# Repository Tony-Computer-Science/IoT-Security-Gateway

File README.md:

# IoT Security Gateway

**CyberGuards, CSE 484.** Two ESP32 gateway boards connect devices on a
private WPA2 access point to an existing Wi-Fi network through a wired link
(SPI by default, with an optional two-wire UART test mode).

```text
Devices -> Board A: WPA2 AP -> SPI/UART -> Board B: Wi-Fi station -> Router -> Internet
```

The board names remain **station-board (A)** and **bridge-board (B)** for
repository compatibility. These names do not describe their new Wi-Fi modes:
A is the access point; B is the upstream station. A third ESP32-C6 or ESP32-S3 (Board C)
joins A's AP and controls an RGB LED through a separate PC web service.

## Repository guide

| Path | Contents |
|---|---|
| [firmware/](firmware/README.md) | Gateway A/B images, Board C LED target, S3 SPI test host and shared components |
| [web/](web/README.md) | Browser interface, real-device PC service and standalone development mock |
| [hardware/](hardware/README.md) | S3 Rev A PCB and separate C6 SPI/UART wiring |
| [docs/](docs/README.md) | Architecture, API/link contracts, client setup, maintenance and testing |
| [tools/test/](tools/test/README.md) | Host protocol tests, HTTP tests, optional Postman checks and echo server |

For local UI work without boards, run `python3 web/mock/server.py` and open
the printed URL. The mock simulates the target; use the real-device service
in the setup below for physical LED control.

## Setting Up

The website and its API are a **separate service running outside the ESP32
boards**. For simplicity, this demo runs that service on a local computer
instead of a dedicated server: **the computer acts as the server**. It joins
**IoT-Gateway** and serves the UI/API at **http://192.168.78.10:8000/**.
Board C has that server IPv4 address and device TLS port **8443**
**compiled into its firmware**
from menuconfig (`TARGET_UI_HOST` / `TARGET_UI_PORT`); it does not discover
the server automatically. Board C contacts it over Wi-Fi; station and bridge
provide networking. No ESP32 hosts the website or browser API.

Before the first run, build/configure and flash each board using the
[station](firmware/station-board/README.md),
[bridge](firmware/bridge-board/README.md) and
[IoT device](firmware/target-device/README.md) instructions. Bridge needs the
upstream Wi-Fi credentials; Board C needs the separate station AP password.
Provision private device identities before the target build using
[PC-only isolation](docs/device-isolation.md). Keep passwords and identities
in private configuration, not this README.

1. **Power on station and bridge.** Keep their configured wired link connected.
   For SPI, match each configured signal at both ends, including handshake and
   common ground; see [C6 wiring](hardware/docs/README.md#esp32-c6-development-board-wiring).
   The current bench uses a private pin-map variant recorded in
   [testing](docs/testing.md). UART is an optional alternative and requires
   matching mode/baud and crossed TX/RX; see [UART wiring](docs/uart-link.md).
   Each board also needs USB power. Check the controllable RGB LEDs against
   the table below. Their identity colors do not prove Wi-Fi or internet access.
2. **Join the station network from a phone and check internet access.** In
   the phone's Wi-Fi settings, join **IoT-Gateway** using the station AP
   password. Temporarily turn off mobile data so the test uses the gateway.
   Open `http://example.com` and confirm the page loads; do not rely only on
   the phone's connection label. If it fails, check that the phone joined
   **IoT-Gateway** and that bridge joined the intended upstream network
   (the configured school network, using passwordless OWE) with
   a valid IP address. Use the troubleshooting
   table below before proceeding with the internet test.
3. **Connect the computer that will host the web service.** Join that computer
   to **IoT-Gateway** too. On the Windows demo PC, set Wi-Fi IPv4 to
   **192.168.78.10**, subnet mask **255.255.255.0**, gateway **192.168.78.1**,
   and the upstream DNS supplied by bridge. Follow the
   [Windows fixed-IP and firewall steps](docs/client-network.md#windows-ui-computer).
   Check `ipconfig` shows .10 on the Wi-Fi adapter. Only this computer should
   use .10; the phone and IoT device obtain addresses automatically.
4. **Start the web service on that computer.** With Python 3.9 or later,
   open a terminal in this repository's root and run:

   ```powershell
   python web/device_server.py --host 192.168.78.10 --port 8000
   ```

   Leave the terminal open. Allow the device TLS listener on TCP 8443 using the
   scoped firewall rule in the Windows guide. On the PC, open
   `http://192.168.78.10:8000/`. Sign in as **operator** with the password
   printed by the service. This login password is separate from the Wi-Fi
   password. Use `device_server.py` for hardware control; the mock server
   only simulates a device. Until Board C connects, unavailable device status
   and disabled command buttons are expected.

   The service also monitors the gateway live: it pings Board A
   (`192.168.78.1`) every 2 s and opens a connection to `1.1.1.1:443` through
   A, the UART link and Board B every 5 s. The control page shows each result
   with a five-minute up/down timeline, and changes appear in the event log.
   The path check is only meaningful while this computer routes through
   Board A, so keep it off other networks (Ethernet, a second Wi-Fi) during
   the demo. Use `--outside IPv4:port` if the upstream network blocks that
   address.
5. **Power on the third C6, the IoT device.** Its firmware must have the
   **IoT-Gateway** SSID/passphrase, service address **192.168.78.10**, port
   **8443** for the authenticated device channel, and device ID **iot-c6**.
   Provision identities before building as described in
   [PC-only isolation](docs/device-isolation.md). It joins Wi-Fi automatically and polls
   the service; it needs no signal jumpers to the other boards. Wait for
   reachable status in the website, then click **Turn on**: its controllable
   RGB LED should become **green** after device confirmation. Click **Turn
   off** and verify it goes dark. Off at startup is expected, not a connection
   failure. Station remains blue and bridge remains red.

| Board | Expected controllable RGB LED |
|---|---|
| Station / A | **Blue**, identifying the station firmware |
| Bridge / B | **Red**, identifying the bridge firmware |
| IoT device / C | **Off at startup**, **green after Turn on**, off after Turn off |

Look at the controllable RGB LED, not the separate power light, which may
stay green. These defaults apply to the matching C6 development boards with
the RGB LED on GPIO8. The phone, service PC and IoT device use three of the
station AP's four default client slots.

If a check fails:

| Symptom | What to check |
|---|---|
| Wrong board color or IoT-Gateway is missing | Confirm power, board labels and the correct firmware image. Check AP configuration and startup logs; a power light alone does not identify the firmware. |
| Phone joins but a webpage cannot load | Confirm mobile data is off, the phone joined IoT-Gateway and DHCP gave it 192.168.78.100–199 with gateway .1. Check bridge's upstream SSID/password and IP, and test that upstream network's internet separately. Check the selected SPI signal mapping/handshake and common ground, or crossed UART wires and matching mode/baud if UART is selected. After bridge is online, reconnect the phone to refresh DHCP/DNS. |
| Service fails to bind to 192.168.78.10 | Confirm the service PC joined IoT-Gateway and .10 is assigned to its Wi-Fi adapter before launch. Check another program is not already using port 8000. |
| Website opens on the PC but not on the phone | Expected: the UI/API admits only the PC itself. Other clients receive 403 if they can reach the listener. |
| Website opens but the device stays unavailable | Confirm Board C is flashed/configured for IoT-Gateway with the AP password, .10:8443, provisioned TLS identities and matching device ID. Keep the real device service running. Inspect Board C's Wi-Fi/poll logs and the PC firewall. The LED can correctly be off while connected. |
| A command has an unknown result | Wait for a fresh device status report before retrying, then compare the reported state with the physical LED. Check service/device logs if confirmation continues to fail. |

Local website and LED control use the station AP and can work without
upstream internet; the phone's internet test checks a separate routing path.
No port forwarding or public exposure is needed for this local demo. A
dedicated server can host the separate service later, but Board C's configured
service IPv4 address/port and outbound network reachability must match that
deployment. The device channel requires mutual TLS; the UI/API is PC-only. See
the [isolation setup and limits](docs/device-isolation.md) and the
[device API and its limitations](docs/device-api.md).

## Current status

- Board B implements personal WPA2/WPA3 or passwordless OWE uplink,
  DHCP/reconnection, a bounded Ethernet-over-SPI/UART transport, IPv4
  routing/NAPT, and restart isolation.
- `firmware/spi-test-host` is a separate Board A test image. Its radio stays
  off; DNS/HTTPS and configurable TCP/UDP echo tests use SPI only.
- Board A implements an AP-only WPA2/AES network, DHCP, DNS propagation and
  client NAT onto SPI. Per-device network policy remains future work; the
  website/API runs as the separate service described above.
- Board C is an ESP32-C6 Wi-Fi LED device that contacts a PC at
  **192.168.78.10:8443** with mutual TLS. The PC serves the website on port 8000 and confirms LED
  commands against device acknowledgements. See [third-board setup](firmware/target-device/README.md).
  S3 physical LED/heartbeat/restart results are recorded in
  [bench evidence](docs/s3-test-evidence.md); the C6/Linux fixed-IP bench passed control; Windows acceptance is pending.
- ESP32-C6 UART hardware checks verified AP/DHCP, phone internet access and
  peer-restart recovery; see [UART results](docs/uart-link.md). The 4 MHz SPI
  bench passed DNS/HTTP with zero malformed frames. Simultaneous clients,
  restart recovery on SPI and extended soak checks remain on the
  [acceptance checklist](docs/testing.md).
- Four Wi-Fi clients are supported by default, with .10 excluded from DHCP
  for a fixed UI PC. See [Windows setup and outbound-only routing](docs/client-network.md).

## Build and use

Use **ESP-IDF 6.1**, ESP32-S3 or ESP32-C6, at least 4 MB flash; PSRAM is not
required. The Rev A PCB and default target remain S3. C6 development boards
use the separate [C6 wiring](hardware/docs/README.md#esp32-c6-development-board-wiring)
and `idf.py set-target esp32c6` in each station/bridge project.
See [Board A instructions](firmware/station-board/README.md),
[Board B instructions](firmware/bridge-board/README.md) and
[test-host instructions](firmware/spi-test-host/README.md) for configuration,
flashing, wiring, and tests. Do not commit generated `sdkconfig` or binaries:
all Wi-Fi firmware binaries contain their configured credentials.

For the third C6, use [Board C instructions](firmware/target-device/README.md).
On the Windows UI PC, run `python web/device_server.py --host 192.168.78.10 --port 8000`
from this repository, then open `http://192.168.78.10:8000/` and use the
operator login printed by the service.

```sh
python3 tools/test/run_host_tests.py
python3 tools/test/test_device_server.py
python3 web/scripts/build.py
```

These local checks need Python 3.9+; protocol tests also need a C compiler
with AddressSanitizer/UndefinedBehaviorSanitizer. Board C parser tests require
its managed cJSON dependency, and the optional collection check requires the
Postman CLI. See [all test commands and prerequisites](docs/testing.md#local-software-checks).

## Design and requirements

This is an intentional change from the original fixed-target command gateway.
Normal internet routing conflicts with the original prohibition on packet
forwarding and with the original command allow-list. The original graded
[R1–R7 text](docs/requirements.md) is preserved verbatim; this milestone does
**not** claim compliance with that design. The differences and remaining
security work are explained in [architecture](docs/architecture.md).

Key references: [SPI contract 0.2.0](docs/spi-protocol.md),
[firmware maintenance](docs/firmware-maintenance.md),
[hardware pinout](hardware/docs/README.md), [contribution rules](CONTRIBUTING.md).
The existing KiCad layout is not fabricated; some silkscreen labels describe
the previous Wi-Fi roles. Rev A PCB wiring is unchanged; C6 boards use their
separate documented pinout.

For a demo with two signal jumpers plus common ground, station and bridge can
use the optional [UART test link](docs/uart-link.md). SPI remains the default.

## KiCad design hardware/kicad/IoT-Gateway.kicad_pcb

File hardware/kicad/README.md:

# hardware/kicad

KiCad 10 project for the gateway PCB: Board A and Board B (two ESP32-S3-WROOM-1
modules) on one 4-layer board, linked only by SPI (SCLK, MOSI, MISO, CS) and
the HS handshake line. Rev A is designed through ERC/DRC-clean outputs but not
fabricated.

## Current owner (provisional)

Carter Cattadoris. Any member may work here; the current owner reviews.

## Contents

| Path | Purpose |
|---|---|
| `IoT-Gateway.kicad_pro` | Project. Open this in KiCad 10 (files can't be opened by KiCad 9 or older) |
| `IoT-Gateway.kicad_sch` | Top sheet; sub-sheets `power.kicad_sch`, `module_a.kicad_sch`, `module_b.kicad_sch` |
| `IoT-Gateway.kicad_pcb` | 100 x 50 mm, 4 layers, JLCPCB JLC04161H-7628 stackup |
| `DESIGN_NOTES.md` | Requirements status, decisions and deviations log, power budget, stackup and routing notes |

Generated outputs (`outputs/`: schematic PDF, BOM, 3D renders, ERC/DRC
reports; `fab/`: Gerbers and drill files) and the Rev A generation scripts
(`scripts/`) are kept locally and git-ignored (see `.gitignore`). Regenerate
outputs from the KiCad files (File → Plot / Fabrication Outputs, or `kicad-cli`).

## Conventions

- Commit `.kicad_pro`, `.kicad_sch`, `.kicad_pcb`, and any project-local
  symbol and footprint libraries.
- Don't commit `*.kicad_prl`, `*-backups/`, or `fp-info-cache` (git-ignored).
- Put fabrication outputs (Gerbers, drill files) in `kicad/fab/` only when
  ordering a board, and tag the commit. `fab/` is git-ignored, so add them
  with `git add -f`.
- KiCad version: this project uses KiCad 10 (team version still to be agreed).

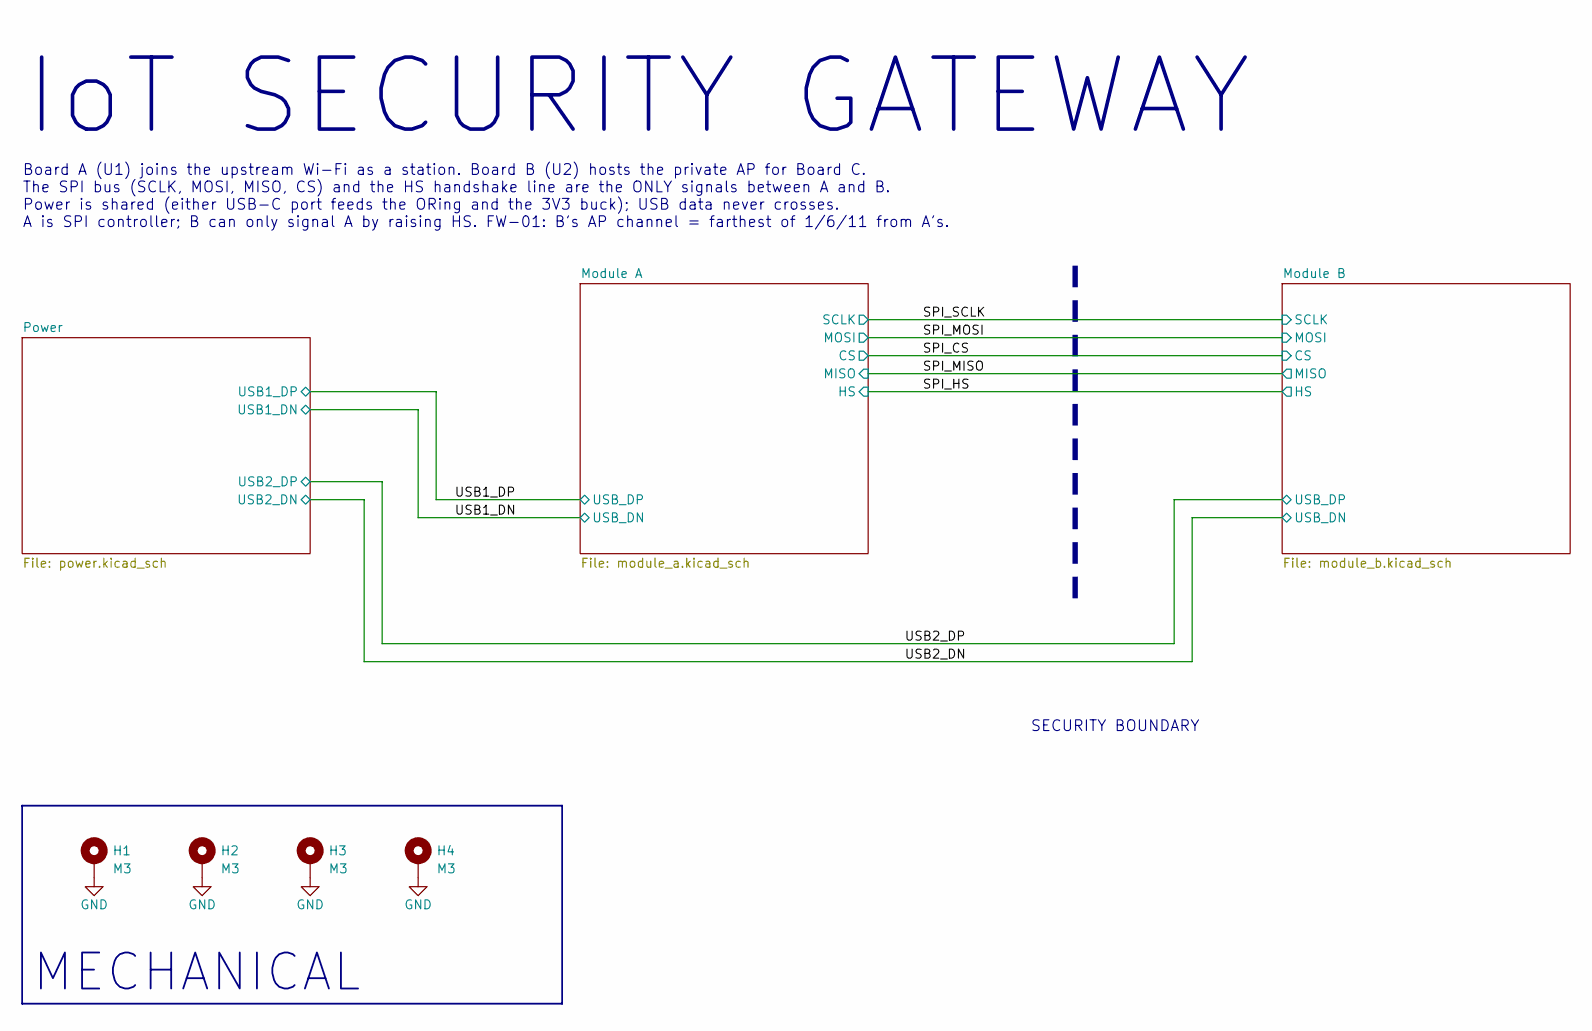
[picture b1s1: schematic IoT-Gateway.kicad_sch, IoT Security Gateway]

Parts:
H1, H2, H3, H4: M3; MountingHole_3.2mm_M3_Pad_Via

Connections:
GND: H1.1, H2.1, H3.1, H4.1; also elsewhere on the board

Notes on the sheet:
MECHANICAL
IoT SECURITY GATEWAY
Board A (U1) joins the upstream Wi-Fi as a station. Board B (U2) hosts the private AP for Board C. The SPI bus (SCLK, MOSI, MISO, CS) and the HS handshake line are the ONLY signals between A and B. Power is shared (either USB-C port feeds the ORing and the 3V3 buck); USB data never crosses. A is SP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
SECURITY BOUNDARY

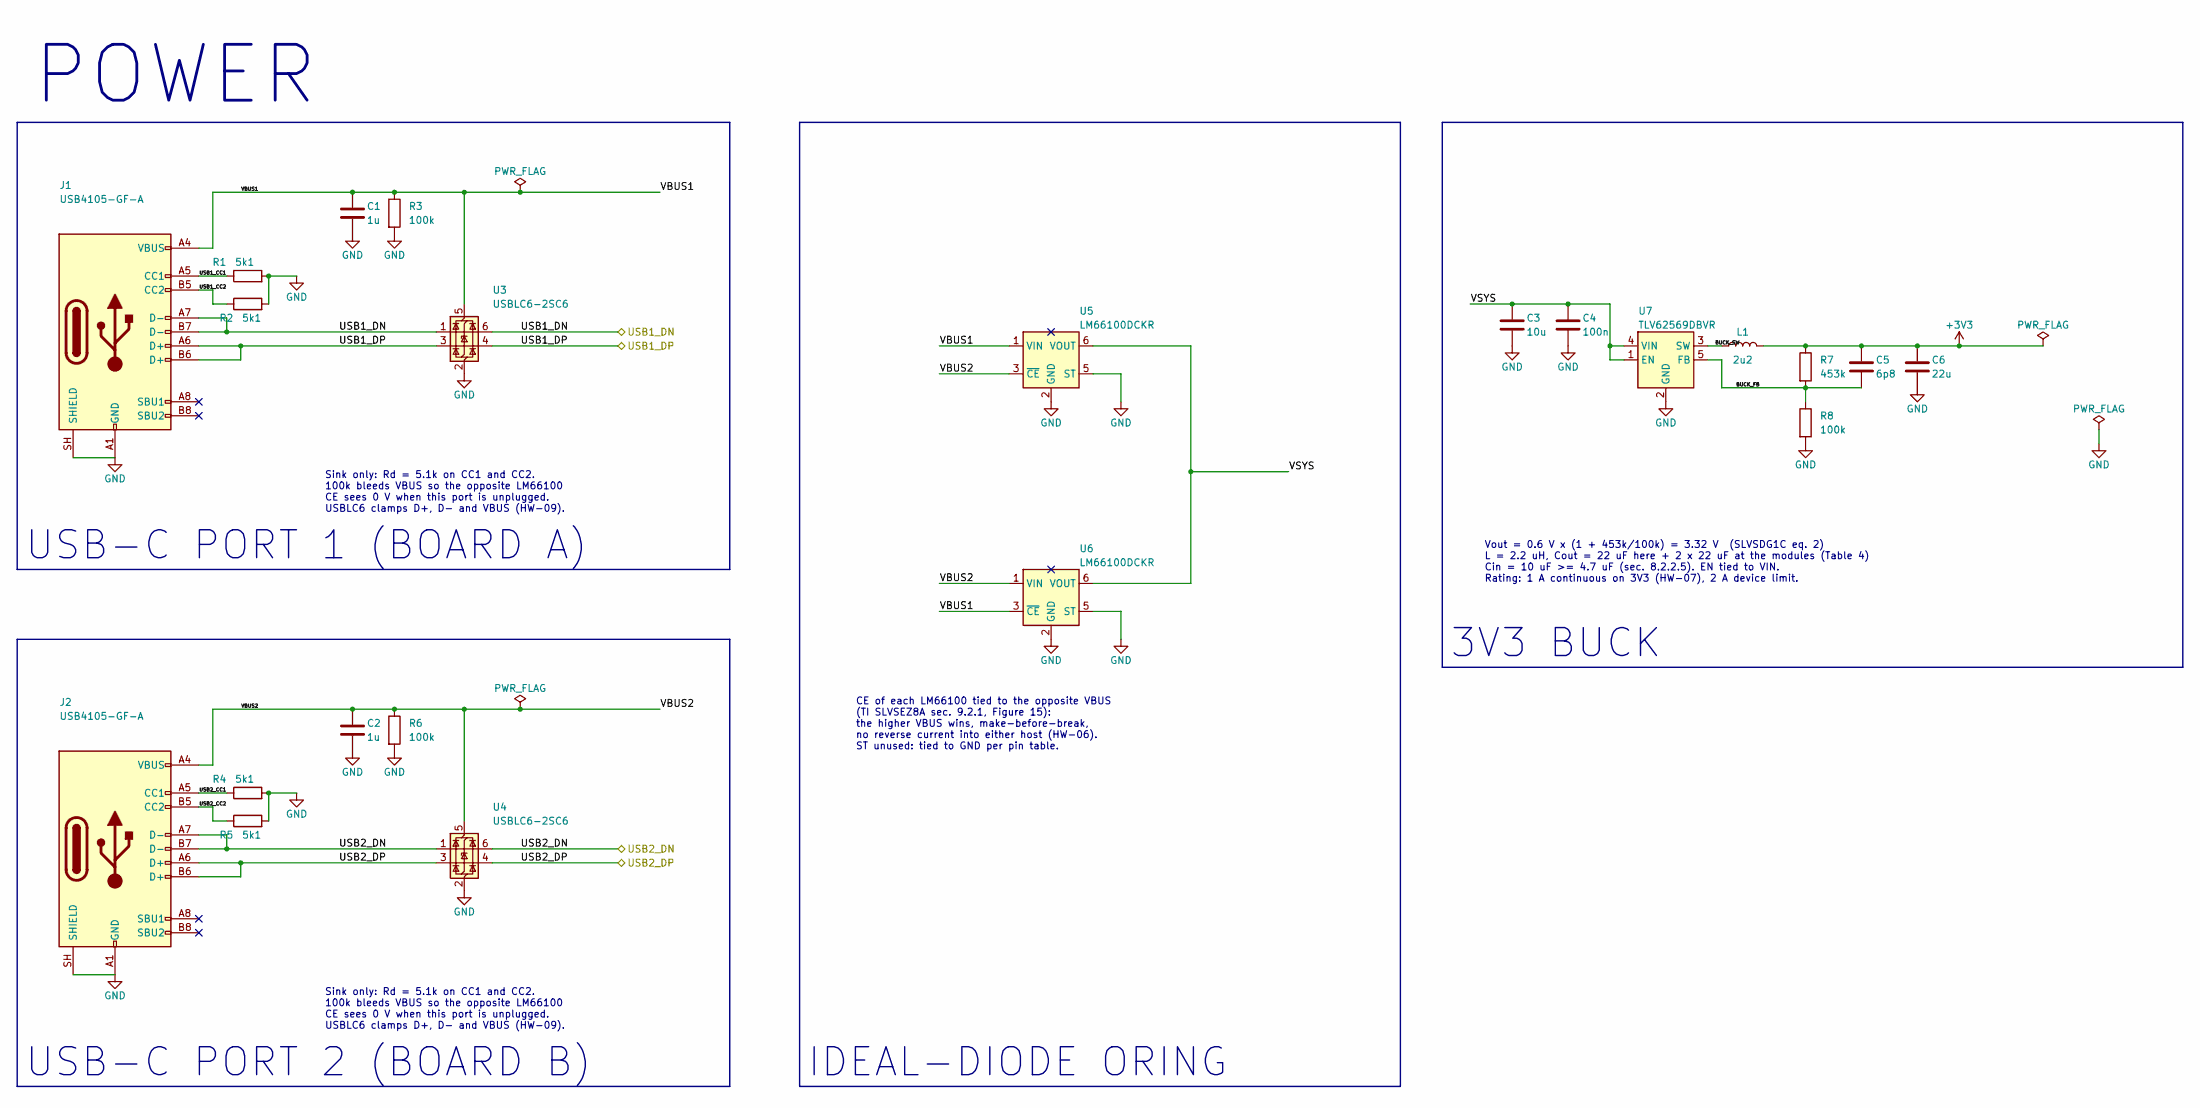
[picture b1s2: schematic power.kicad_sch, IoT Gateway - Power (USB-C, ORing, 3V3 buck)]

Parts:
C1, C2: 1u; C_0603_1608Metric
C3: 10u; C_0805_2012Metric
C4: 100n; C_0603_1608Metric
C5: 6p8; C_0603_1608Metric
C6: 22u; C_0805_2012Metric
J1, J2: USB4105-GF-A; USB_C_Receptacle_GCT_USB4105-xx-A_16P_TopMnt_Horizontal; Mfg Part # USB4105-GF-A
L1: 2u2; L_Coilcraft_XAL4020-XXX; Mfg Part # XAL4020-222ME
R1, R2, R4, R5: 5k1; R_0603_1608Metric
R3, R6, R8: 100k; R_0603_1608Metric
R7: 453k; R_0603_1608Metric
U3, U4: USBLC6-2SC6; SOT-23-6; Mfg Part # USBLC6-2SC6
U5, U6: LM66100DCKR; SOT-363_SC-70-6; Mfg Part # LM66100DCKR
U7: TLV62569DBVR; SOT-23-5; Mfg Part # TLV62569DBVR

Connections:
+3V3: C5.1, C6.1, L1.2, R7.1; also elsewhere on the board
/Power/BUCK_FB: C5.2, R7.2, R8.1, U7.5 (FB)
/Power/BUCK_SW: L1.1, U7.3 (SW)
/Power/USB1_CC1: J1.A5 (CC1), R1.1
/Power/USB1_CC2: J1.B5 (CC2), R2.1
/Power/USB2_CC1: J2.A5 (CC1), R4.1
/Power/USB2_CC2: J2.B5 (CC2), R5.1
/Power/VBUS1: C1.1, J1.A4 (VBUS), J1.A9 (VBUS), J1.B4 (VBUS), J1.B9 (VBUS), R3.1, U3.5 (VBUS), U5.1 (VIN), U6.3 (~CE)
/Power/VBUS2: C2.1, J2.A4 (VBUS), J2.A9 (VBUS), J2.B4 (VBUS), J2.B9 (VBUS), R6.1, U4.5 (VBUS), U5.3 (~CE), U6.1 (VIN)
/Power/VSYS: C3.1, C4.1, U5.6 (VOUT), U6.6 (VOUT), U7.1 (EN), U7.4 (VIN)
/USB1_DN: J1.A7 (D-), J1.B7 (D-), U3.1 (I/O1), U3.6 (I/O1); also elsewhere on the board
/USB1_DP: J1.A6 (D+), J1.B6 (D+), U3.3 (I/O2), U3.4 (I/O2); also elsewhere on the board
/USB2_DN: J2.A7 (D-), J2.B7 (D-), U4.1 (I/O1), U4.6 (I/O1); also elsewhere on the board
/USB2_DP: J2.A6 (D+), J2.B6 (D+), U4.3 (I/O2), U4.4 (I/O2); also elsewhere on the board
GND: C1.2, C2.2, C3.2, C4.2, C6.2, J1.A1 (GND), J1.A12 (GND), J1.B1 (GND), J1.B12 (GND), J1.SH (SHIELD), J2.A1 (GND), J2.A12 (GND), J2.B1 (GND), J2.B12 (GND), J2.SH (SHIELD), R1.2, R2.2, R3.2, R4.2, R5.2, R6.2, R8.2, U3.2 (GND), U4.2 (GND), U5.2 (GND), U5.5 (ST), U6.2 (GND), U6.5 (ST), U7.2 (GND); also elsewhere on the board

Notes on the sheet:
USB-C PORT 1 (BOARD A)
Sink only: Rd = 5.1k on CC1 and CC2. 100k bleeds VBUS so the opposite LM66100 CE sees 0 V when this port is unplugged. USBLC6 clamps D+, D- and VBUS (HW-09).
USB-C PORT 2 (BOARD B)
IDEAL-DIODE ORING
CE of each LM66100 tied to the opposite VBUS (TI SLVSEZ8A sec. 9.2.1, Figure 15): the higher VBUS wins, make-before-break, no reverse current into either host (HW-06). ST unused: tied to GND per pin table.
3V3 BUCK
Vout = 0.6 V x (1 + 453k/100k) = 3.32 V (SLVSDG1C eq. 2) L = 2.2 uH, Cout = 22 uF here + 2 x 22 uF at the modules (Table 4) Cin = 10 uF >= 4.7 uF (sec. 8.2.2.5). EN tied to VIN. Rating: 1 A continuous on 3V3 (HW-07), 2 A device limit.
POWER

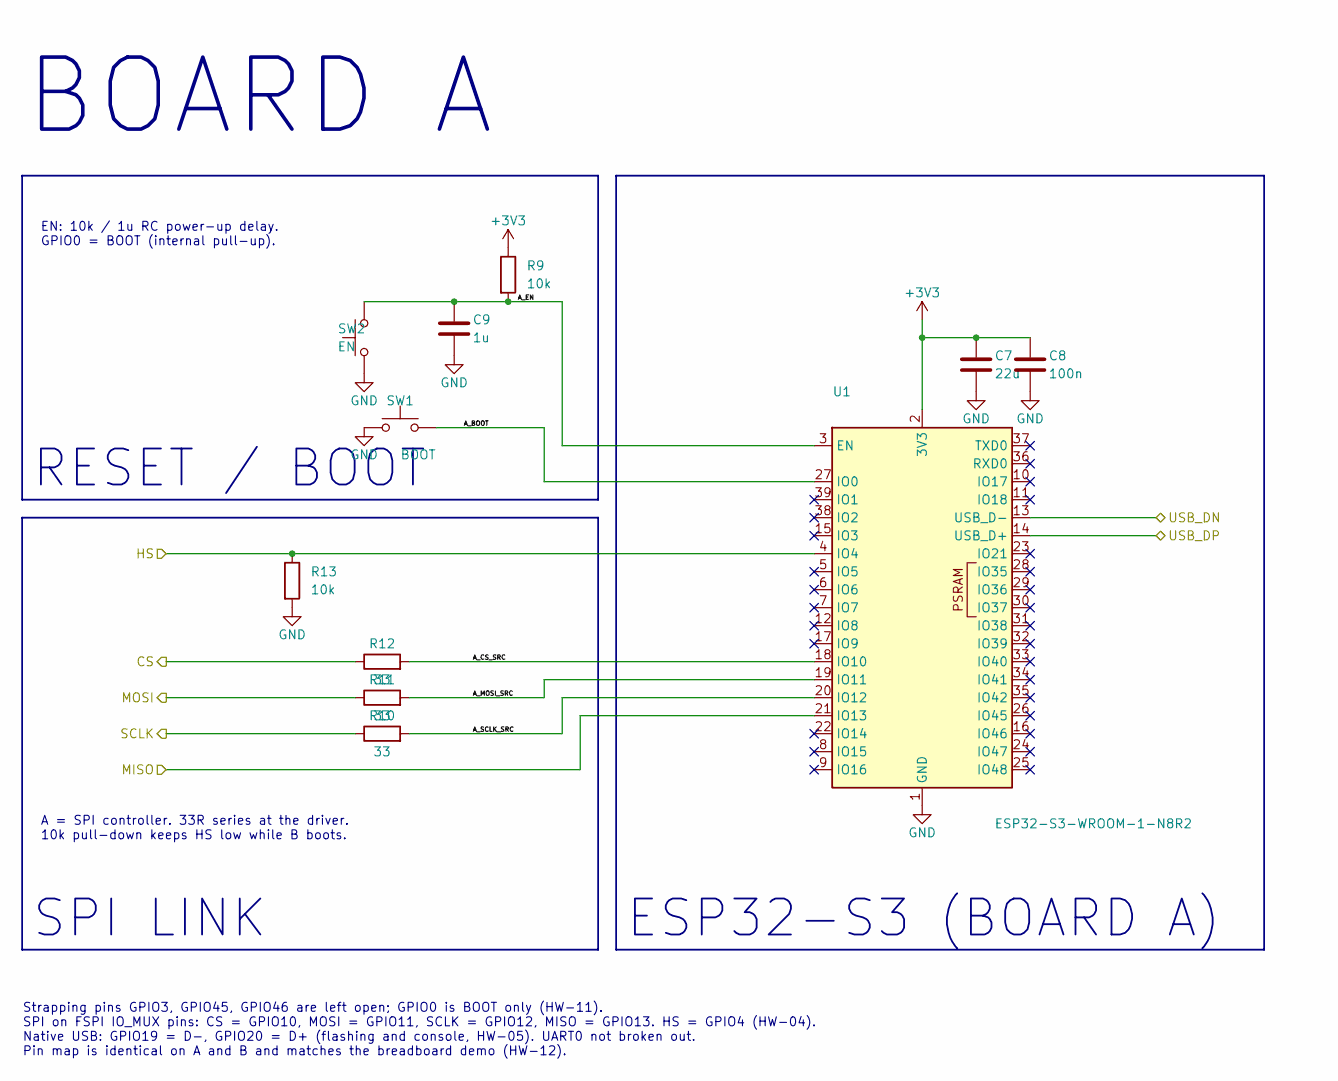
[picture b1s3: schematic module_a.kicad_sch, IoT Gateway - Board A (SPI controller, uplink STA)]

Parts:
C7: 22u; C_0805_2012Metric
C8: 100n; C_0603_1608Metric
C9: 1u; C_0603_1608Metric
R9, R13: 10k; R_0603_1608Metric
R10, R11, R12: 33; R_0603_1608Metric
SW1: BOOT; SW_SPST_B3U-1000P
SW2: EN; SW_SPST_B3U-1000P
U1: ESP32-S3-WROOM-1-N8R2; ESP32-S3-WROOM-1; Mfg Part # ESP32-S3-WROOM-1-N8R2

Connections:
+3V3: C7.1, C8.1, R9.1, U1.2 (3V3); also elsewhere on the board
/Module A/A_BOOT: SW1.2, U1.27 (IO0)
/Module A/A_CS_SRC: R12.2, U1.18 (IO10)
/Module A/A_EN: C9.1, R9.2, SW2.2, U1.3 (EN)
/Module A/A_MOSI_SRC: R11.2, U1.19 (IO11)
/Module A/A_SCLK_SRC: R10.2, U1.20 (IO12)
/SPI_CS: R12.1; also elsewhere on the board
/SPI_HS: R13.1, U1.4 (IO4); also elsewhere on the board
/SPI_MISO: U1.21 (IO13); also elsewhere on the board
/SPI_MOSI: R11.1; also elsewhere on the board
/SPI_SCLK: R10.1; also elsewhere on the board
/USB1_DN: U1.13 (USB_D-); also elsewhere on the board
/USB1_DP: U1.14 (USB_D+); also elsewhere on the board
GND: C7.2, C8.2, C9.2, R13.2, SW1.1, SW2.1, U1.1 (GND), U1.40 (GND), U1.41 (GND); also elsewhere on the board

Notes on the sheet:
ESP32-S3 (BOARD A)
RESET / BOOT
EN: 10k / 1u RC power-up delay. GPIO0 = BOOT (internal pull-up).
SPI LINK
A = SPI controller. 33R series at the driver. 10k pull-down keeps HS low while B boots.
Strapping pins GPIO3, GPIO45, GPIO46 are left open; GPIO0 is BOOT only (HW-11). SPI on FSPI IO_MUX pins: CS = GPIO10, MOSI = GPIO11, SCLK = GPIO12, MISO = GPIO13. HS = GPIO4 (HW-04). Native USB: GPIO19 = D-, GPIO20 = D+ (flashing and console, HW-05). UART0 not broken out. Pin map is identical on A 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
BOARD A

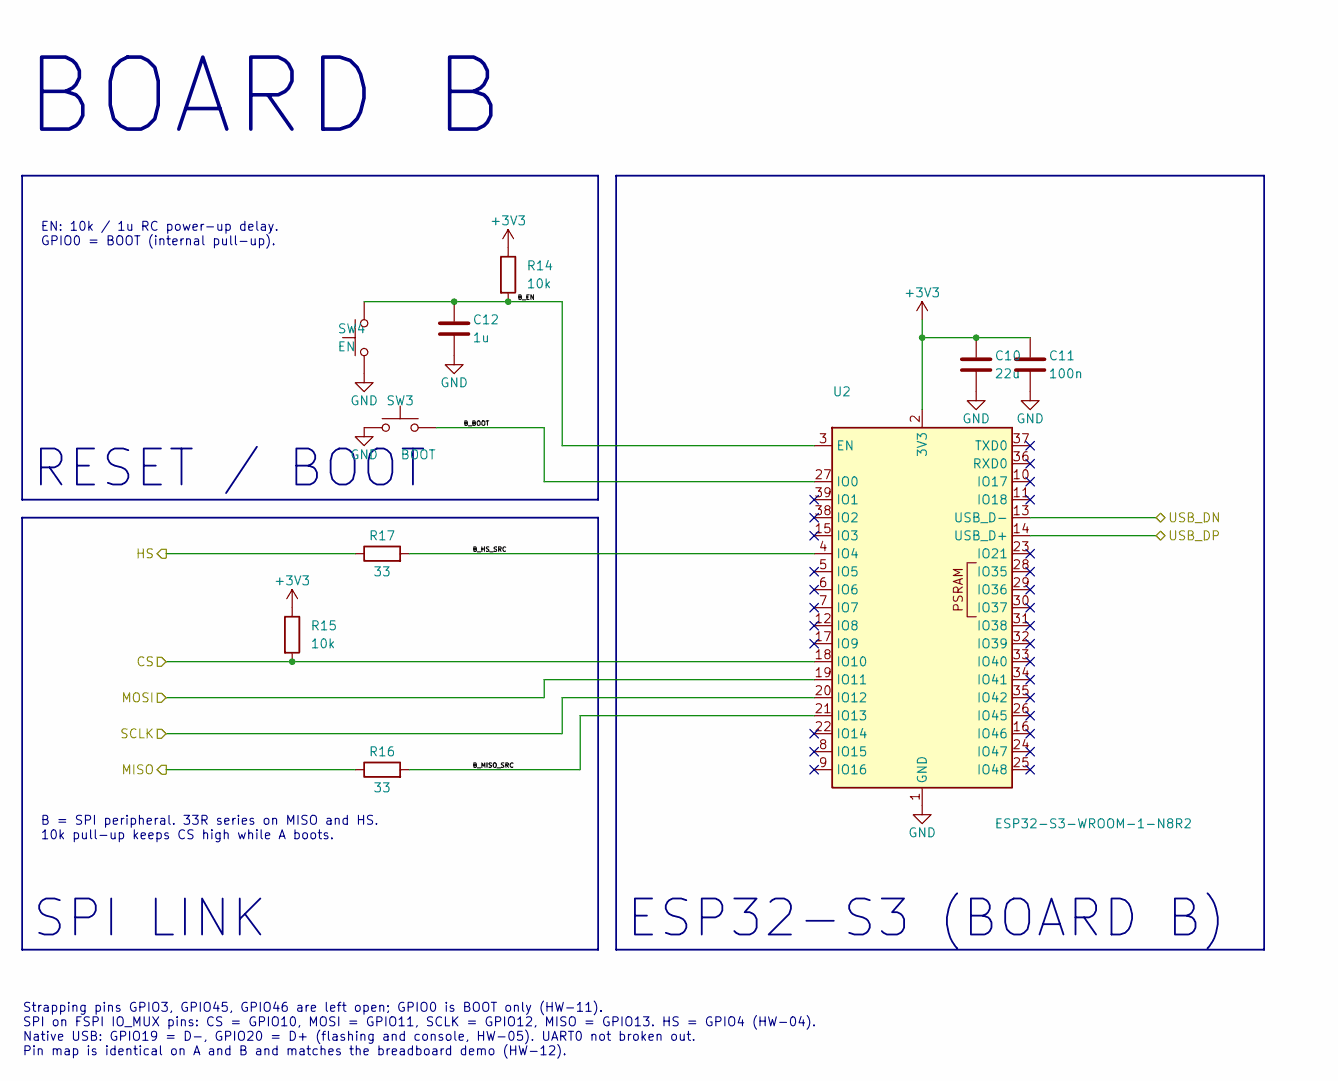
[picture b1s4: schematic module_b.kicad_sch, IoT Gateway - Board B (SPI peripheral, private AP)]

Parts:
C10: 22u; C_0805_2012Metric
C11: 100n; C_0603_1608Metric
C12: 1u; C_0603_1608Metric
R14, R15: 10k; R_0603_1608Metric
R16, R17: 33; R_0603_1608Metric
SW3: BOOT; SW_SPST_B3U-1000P
SW4: EN; SW_SPST_B3U-1000P
U2: ESP32-S3-WROOM-1-N8R2; ESP32-S3-WROOM-1; Mfg Part # ESP32-S3-WROOM-1-N8R2

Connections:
+3V3: C10.1, C11.1, R14.1, R15.1, U2.2 (3V3); also elsewhere on the board
/Module B/B_BOOT: SW3.2, U2.27 (IO0)
/Module B/B_EN: C12.1, R14.2, SW4.2, U2.3 (EN)
/Module B/B_HS_SRC: R17.2, U2.4 (IO4)
/Module B/B_MISO_SRC: R16.2, U2.21 (IO13)
/SPI_CS: R15.2, U2.18 (IO10); also elsewhere on the board
/SPI_HS: R17.1; also elsewhere on the board
/SPI_MISO: R16.1; also elsewhere on the board
/SPI_MOSI: U2.19 (IO11); also elsewhere on the board
/SPI_SCLK: U2.20 (IO12); also elsewhere on the board
/USB2_DN: U2.13 (USB_D-); also elsewhere on the board
/USB2_DP: U2.14 (USB_D+); also elsewhere on the board
GND: C10.2, C11.2, C12.2, SW3.1, SW4.1, U2.1 (GND), U2.40 (GND), U2.41 (GND); also elsewhere on the board

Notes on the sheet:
ESP32-S3 (BOARD B)
RESET / BOOT
EN: 10k / 1u RC power-up delay. GPIO0 = BOOT (internal pull-up).
SPI LINK
B = SPI peripheral. 33R series on MISO and HS. 10k pull-up keeps CS high while A boots.
Strapping pins GPIO3, GPIO45, GPIO46 are left open; GPIO0 is BOOT only (HW-11). SPI on FSPI IO_MUX pins: CS = GPIO10, MOSI = GPIO11, SCLK = GPIO12, MISO = GPIO13. HS = GPIO4 (HW-04). Native USB: GPIO19 = D-, GPIO20 = D+ (flashing and console, HW-05). UART0 not broken out. Pin map is identical on A 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
BOARD B

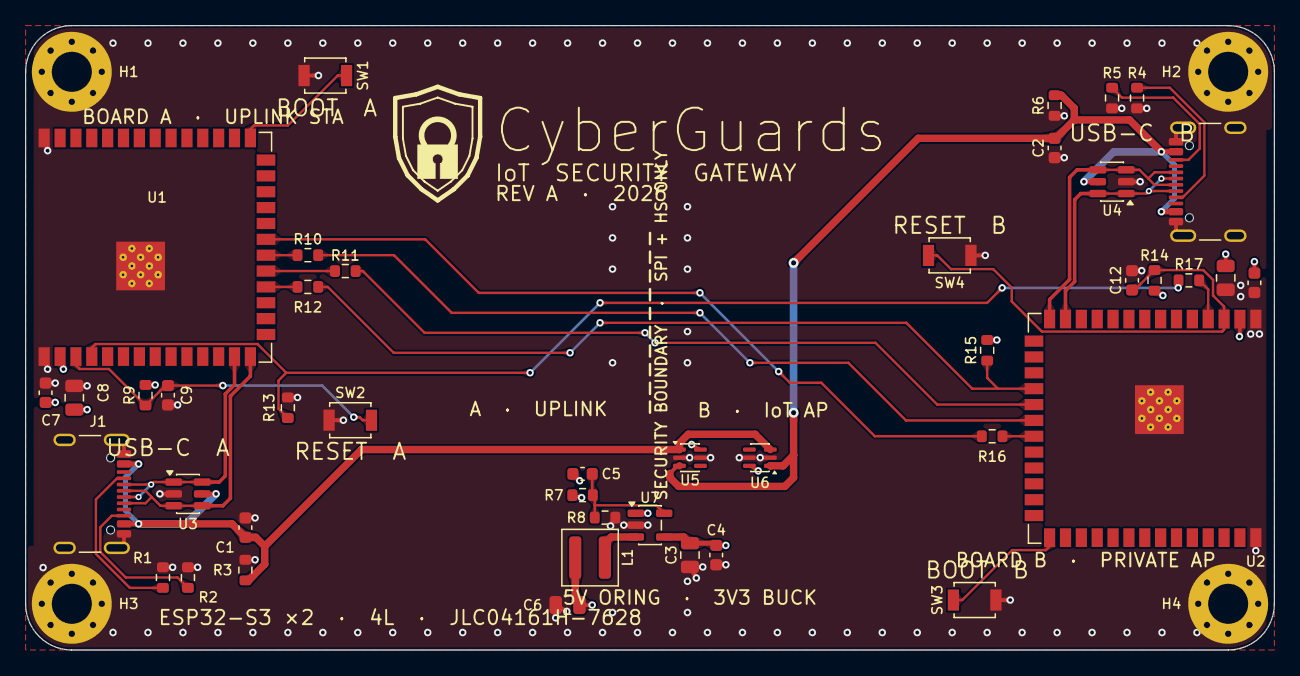
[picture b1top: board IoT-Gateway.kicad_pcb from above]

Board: 4 copper layers, 100.0 x 50.0 mm, 47 parts (0 on the bottom side), 29 nets.
